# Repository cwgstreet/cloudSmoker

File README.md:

<div align="right">
  
</div>
<br>

---

#  cloudSmoker2

# :construction: **Under Development**

⚠️ **Version 2 Notice:** 
<br>

**This is the active development 
branch for cloudSmoker V2. The original design is now deprecated but remains available on the v1-legacy branch.**

___

# Project Summary

The **cloudSmoker** is a WiFi-enabled barbeque temperature monitor designed to take the guesswork out of low-and-slow cooks. 

Building on the reliable foundation of the original cloudSmoker1 2022 release, Version 2 modernises the platform with a focus on precision, expanded capabilities, and a more comprehensive hardware design.

### What’s New in cloudSmoker2
*   **Expanded Monitoring:** Now supports up to four temperature probes for lager cooks.
*   **Enhanced Precision:** Improved measurement accuracy and response via higher-resolution ADC, optimised bias resistor selection plus improved filtering and ADC management.
*   **Modern Hardware:** Upgraded to a contemporary microcontroller, a refreshed display, and a custom 3D-printed enclosure.
*   **Professional Build:** Transitioning to a custom-manufactured PCB using contemporary SMD (Surface Mount) components for increased reliability and a more compact footprint.
*   **Refined Software:** Features seamless OTA (Over-The-Air) firmware updates, streamlined configuration menus, and robust exception monitoring.

### How it Works
The device tracks critical data points, such as pit and internal meat temperatures, and syncs them to an IoT dashboard. This allows for remote monitoring of real-time graphs and gauges from any browser or smartphone. 

To ensure the cook stays on track, the system sends push notifications if temperatures drift or once the meat reaches its target. The project is designed to be cooker-agnostic, making it a reliable companion for a variety of smokers and BBQ setups.

> ### 🌟 **Update:** cloudSmoker2 development is progressing!
>
1) **Boards now built and firmware port / enhancement is underway.**

<br clear="left"/>
<br>

2) **3D printed enclosure design well advanced**

<br clear="left"/>
<br>

<br>
<br>
<br>
<br>

---

<br>

<br>

# cloudSmoker (v1-legacy) #

## 📜 Legacy Support (Version 1.0)
The original version of this project was based on an **ESP8266** and was built on **Veroboard**. While it is no longer the main focus of development, you can still access all the original files:

*   **[Version 1.0 Release Page](https://github.com/cwgstreet/cloudSmoker/releases/tag/v1.0)**
    *   `Hardware_v1.0.zip`: Includes Fritzing layouts, PDF schematics, and build photos.
    *   `Firmware_v1.0.zip`: The stable code and compiled `.bin` for the original build.

<!-- >**Note:** If you are building this project for the first time, we recommend using the **Version 2** PCB files found in this main branch. -->

**WiFi BBQ Temperature Monitor Project**

[comment]: <> (This project exists as a hands-on opportunity to learn more about electronics, IoT, Arduino / ESP8266 programming, GitHub markdown, etc)

<br>

<p align="center">
  
</p>

### Updates (ver1)
1. **Removed pitTemp probe plug-in checks** - no longer displays LCD error or transmits pitTemp values to ThingSpeak if pit temperature probe is unplugged; necessary to allow pitTemp probe to be unplugged after meat is taken off grill so that resting meat temps can continue to be monitored (common to rest briskett in faux cambo for ~1 hour after removing meat from grill).
<br>
<br>

## Project Summary

The cloudSmoker Barbecue Monitor project is a WiFi-enable temperature monitor.  cloudSmoker is designed to read two temperatures (pit and internal meat temperatures) within my Weber BBQ smoker and upload these to an IOT dashboard, allowing remote cloud monitoring of the cook progress showing temperature vs time graphs, gauges, etc, user-definable cooking notification setpoints and exception push notifications to my smartphone, say if the pit temperatures go outside of acceptable ranges and when the meat is done and ready to be removed.

The overall process flow is conceptualised as follows:

Hardware is based around the NodeMCU (V1.0) ESP8266-12E microcontroller module (for both for WiFi access and microcontroller), two Maverick ET-732/733 thermistor probes, an external ADS1015 "12-bit" ADC, plus a 1602 LCD and rotary encoder for user set-up configuration and display.  Minor thermistor and power filtering was also employed for stability.  

Coding was done using VS Code / PlatformIO IDE platform with data uploaded to ThingSpeak for display and further processing.   Push exception notifications are done through Twitter using Thingspeak's React / ThingTweet functionality.  (:warning: Todo:  export cook logs to Google Sheets).

### Project Overview  ###

An extensive project overview and design process description can be found in the project [Wiki](https://github.com/cwgstreet/cloudSmoker/wiki) covering design goals, hardware, software, etc.  

### Hardware ###

The Hardware folder contains KiCad schematic, PCB board layouts (:warning: TODO) and selected datasheets (including the datasheet for the Semitec 105GT-2 Thermistor, that Maverick customer support kindly provided me.   👏 👍

Note that I have not found this datasheet available anywhere on the web and many other projects incorrectly characterised the Maverick ET-732/733 probes as being based on a 10k ohm thermistor (when it's actually 1M ohm!).  This incorrect assumption frequently led to poor bias resistor selection, resulting in poor measurement accuracy.  As a result, these Maverick thermistors were often not highly regarded.  For example, one project concluded they were [acceptable, but not recommended thermistor choice](https://github.com/CapnBry/HeaterMeter/wiki/HeaterMeter-Probes).   

### cloudSmoker ###

This folder contains the full cloudSmoker software (sketch and libraries); developed under VSCode / Platformio IDE rather than Arduino IDE so folder structure reflect Platformio structure.  Note that the project code base is over 1600 lines total and makes extensive use of user and public libraries.

### Images ###

Self-explanatory

### Project Dashboard ###
A public ThingSpeak [cloudSmoker dashboard](https://thingspeak.com/channels/1679986) is available

### Licence ###

**cloudSmoker (ver1):** MIT Licence.  Note that licence terms have changed for cloudSmoker2 (Ver2)

--- END ---

<br>
<br>

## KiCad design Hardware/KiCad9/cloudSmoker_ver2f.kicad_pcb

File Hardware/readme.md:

# cloudSmoker2 Hardware Reference

This directory serves as the root hardware repository for the **cloudSmoker2** platform. It contains mechanical housing documents, sensor calibration resources, manufacturing documentation, and the complete electronic design suite.

---

## 📂 Repository Structure

```text
├── KiCad9/                          # Core ECAD design environment (KiCad 9.x)
│   ├── cloudSmoker_ver2f.kicad_pro  # Main project configuration
│   ├── cloudSmoker_ver2f.kicad_sch  # 4-Layer Schematic blueprints
│   ├── cloudSmoker_ver2f.kicad_pcb  # Mixed-signal PCB layout 
│   ├── sym-lib-table & fp-lib-table # Local dependency resolution tables
│   ├── JLCImport.pretty/            # Component footprints (.kicad_mod)
│   ├── JLCImport.3dshapes/          # 3D structural clearance models (.step / .wrl)
│   ├── production/                  # Manufacturing artifacts (Gerbers, BOM, CPL)
│   └── svg_files/                   # Dynamic high-resolution hardware dashboard graphics
│
├── Thermistor datasheet/            # High-temperature physical probe reference material
│   ├── ET-732 (Thermistor) datasheet scan.pdf
│   └── Maverick ET-732 - 733 (Semitec 105GT-2 Thermistor) datasheet.pdf
│
├── arduino_housing_01_160717_CAD.PDF.pdf   # Mechanical chassis reference dimensions (cloudSmoker1)
└── licence.md                               # Open-source hardware licensing framework
```

## ⚙️ Key File Subsystems

### 1. Electronic Design Automation (`KiCad9/`)
* **ECAD Engine**: Engineered exclusively inside **KiCad 9**. Backward-compatibility issues can occur if parsed with older software builds.
* **Component Portability**: Component symbols, tracking pads, and 3D packages are completely containerized locally inside the `JLCImport` folders. External global library paths are not required to audit the board.
* **Fabrication Files**: The `KiCad9/production/` subdirectory houses pre-compiled fabrication packages including the zipped Gerber layer arrays, coordinates tables (`positions.csv`), and structural parts listings (`bom.csv`).

### 2. Thermistor Data
* **`Thermistor datasheet/`**: Houses structural lookup sheets for the Semitec 105GT-2 high-temp food probes.

### 3. Physical & Enclosure Overlays
* **`arduino_housing_01_160717_CAD.PDF.pdf`**: Legacy cloudSmoker1 mechanical profile drawing used to verify PCB perimeter cuts, mounting hole positions, and connector face alignments against existing chassis designs.

---

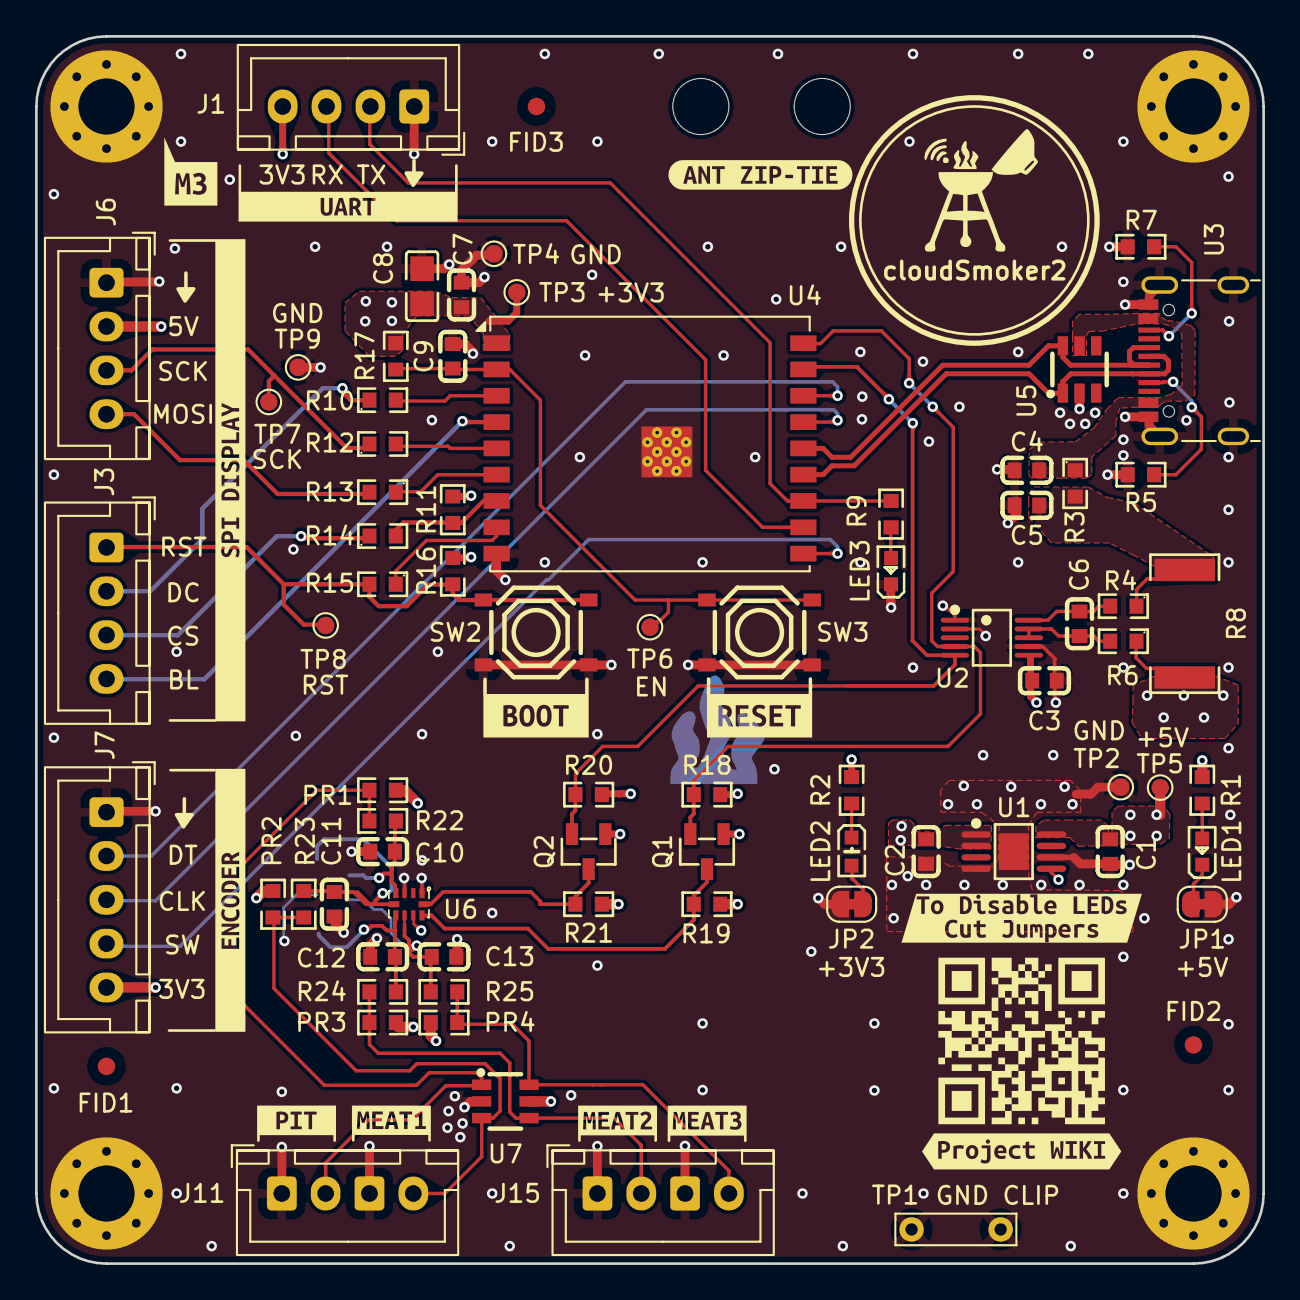
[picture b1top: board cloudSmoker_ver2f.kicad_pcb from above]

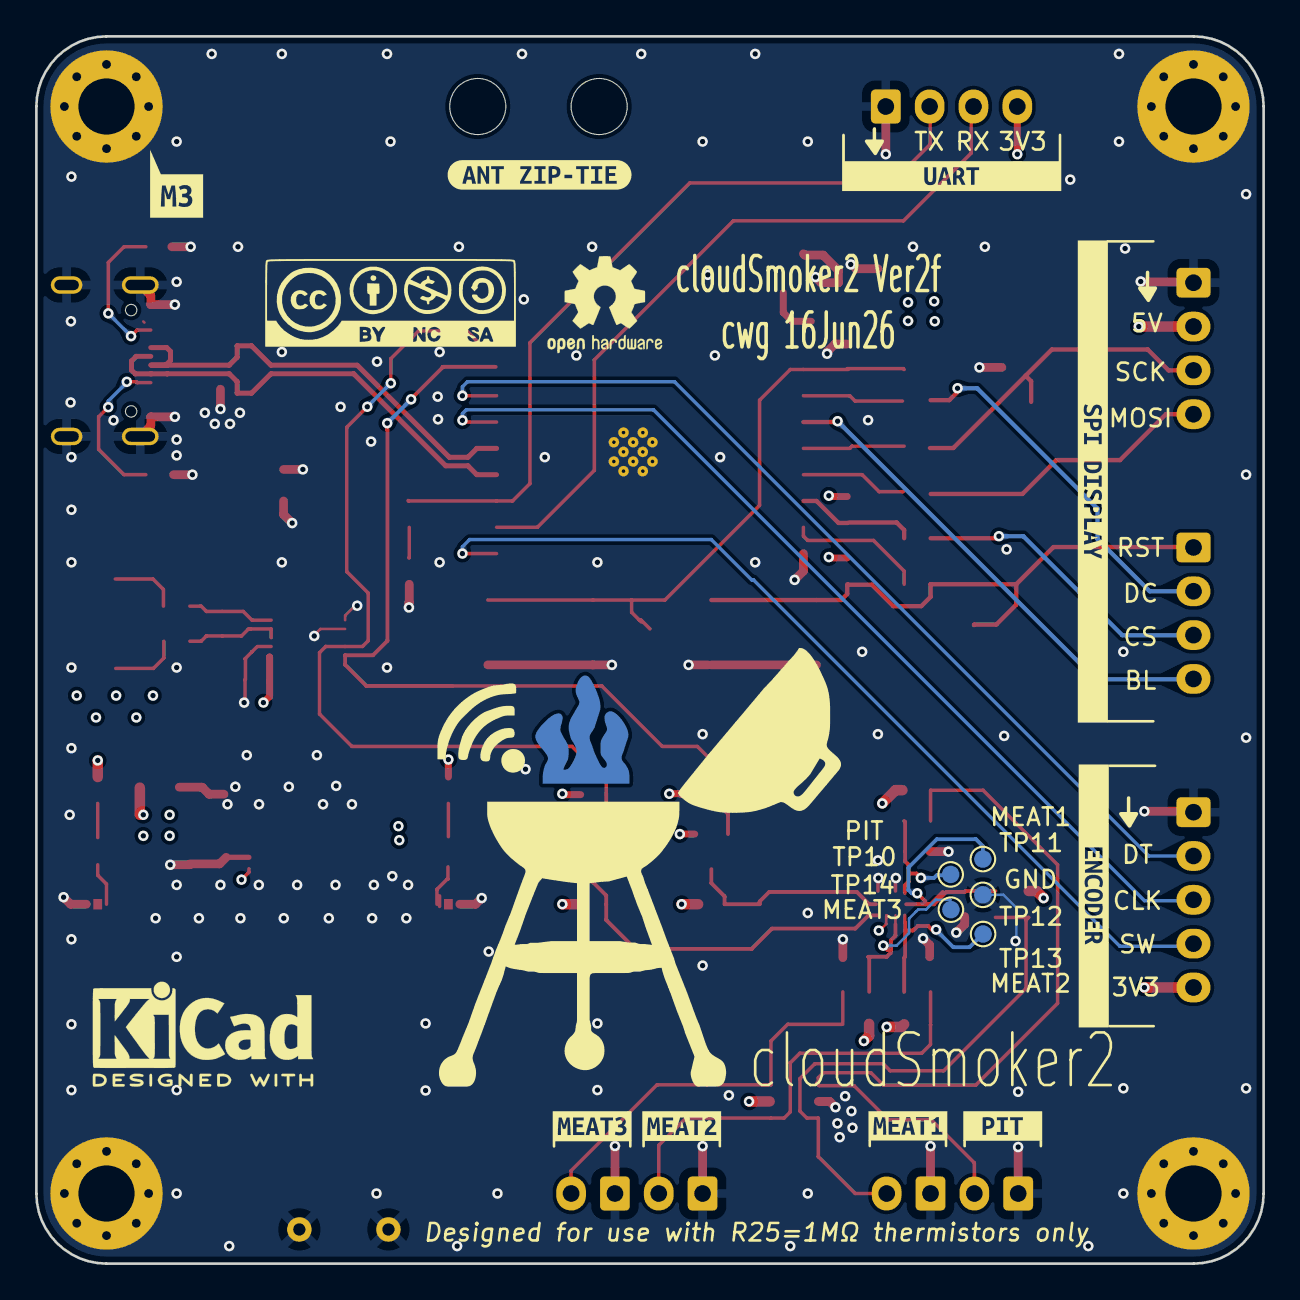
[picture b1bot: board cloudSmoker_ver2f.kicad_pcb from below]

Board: 4 copper layers, 70.0 x 70.0 mm, 110 parts (14 on the bottom side), 45 nets.

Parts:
C1, C9, C10, C11, C12, C13: 1uF; CL10A105KB8NNNC
C2: 2.2uF; CL10A225KO8NNNC
C3, C6, C7: 100nF; CC0603KRX7R9BB104
C4, C5: 470nF; CC0603KRX7R9BB104
C8: 10uF; CL21A106KAYNNNE
FID1, FID2, FID3: Fiducial; Fiducial_1mm_Mask2mm
H1, H2, H3, H4: M3; MountingHole_3.2mm_M3_Pad_Via
H5, H6: M3; MountingHole_3.2mm_M3
J1: Conn_01x02_Pin; JST_XH_B4B-XH-A_1x04_P2.50mm_Vertical
J3, J6: Conn_01x04_Pin; JST_XH_B4B-XH-A_1x04_P2.50mm_Vertical
J7: Conn_01x05; JST_XH_B5B-XH-A_1x05_P2.50mm_Vertical
J11, J15: Conn_01x04_Pin; JST_XH_B4B-XH-A_1x04_P2.50mm_Vertical_two_gnd
JP1, JP2: SolderJumper_2_Bridged; SolderJumper-2_P1.3mm_Bridged_RoundedPad1.0x1.5mm
LED1: Red; KT-0603R
LED2: White; 0603White_light_C2290
LED3: Yellow; FC-1608YXK-585F08
PR1, PR2, PR3, PR4: 120k 0.1%TF; PTFR0603B120KP9
Q1, Q2: BSS138; BSS138_C7420339
QR*****: QR-Code_cloudSmoker_Github_wiki
R1: 2.2k; 0603WAF2201T5E
R2: 1k; 0603WAF1001T5E
R3: 0 ohm; R0603_part-C21189_0-ohm
R4, R6: 10; R0603_part-C22859_10-ohm
R5, R7, R18, R20: 5.1k; 0603WAF5101T5E
R8: 100 mOhm Shunt; RLP25FEER100
R9: 100; 0603WAF1000T5E
R10, R12, R13, R14, R15: 22; R0603_part-C23345
R11, R16, R17, R19, R21, R22, R23, R24, R25: 10k; 0603WAF1002T5E
SW2, SW3: SW_Push_Dual; TS-1187A-B-A-B
TP1: TP_GND_Clip; TestPoint_Bridge_Pitch5.08mm_Drill0.7mm
TP2, TP4, TP9: TP_GND; TestPoint_Pad_D1.0mm
TP3: TP_3V3; TestPoint_Pad_D1.0mm
TP5: TP_5V; TestPoint_Pad_D1.0mm
TP6: TP_EN; TestPoint_Pad_D1.0mm
TP7: TP_SPI_SCK; TestPoint_Pad_D1.0mm
TP8: TP_GIO9; TestPoint_Pad_D1.0mm
TP10: TP_Pit; TestPoint_Pad_D1.0mm
TP11: TP_Meat1; TestPoint_Pad_D1.0mm
TP12: TP_AGND; TestPoint_Pad_D1.0mm
TP13: TP_Meat2; TestPoint_Pad_D1.0mm
TP14: TP_Meat3; TestPoint_Pad_D1.0mm
U1: TLV76733DGNR
U2: INA226AIDGSR
U3: GT-USB-7010ASV; USB_C_Receptacle_G-Switch_GT-USB-7010ASV clipped
U4: ESP32-C3-WROOM-02U-N4; ESP32-C3-WROOM-02U
U5, U7: SRV05-4-P-T7
U6: ADS1115IRUGR
kibuzzard-6A0E9251: G***; kibuzzard-6A0E9251
kibuzzard-6A0E9267: G***; kibuzzard-6A0E9267
kibuzzard-6A1EB0C4, kibuzzard-6A1EB0C4#2: G***; kibuzzard-6A1EB0C4
kibuzzard-6A28B67F, kibuzzard-6A28B67F#2: G***; kibuzzard-6A28B67F
kibuzzard-6A265CBA, kibuzzard-6A265CBA#2: G***; kibuzzard-6A265CBA
kibuzzard-6A265DB6, kibuzzard-6A265DB6#2: G***; kibuzzard-6A265DB6
kibuzzard-6A265E44, kibuzzard-6A265E44#2: G***; kibuzzard-6A265E44
kibuzzard-6A265EBE, kibuzzard-6A265EBE#2: G***; kibuzzard-6A265EBE
kibuzzard-6A266C13: G***; kibuzzard-6A266C13
kibuzzard-6A2660A1, kibuzzard-6A2660A1#2: G***; kibuzzard-6A2660A1
kibuzzard-6A262764, kibuzzard-6A262764#2: G***; kibuzzard-6A262764
kibuzzard-6A266895, kibuzzard-6A266895#2: G***; kibuzzard-6A266895
kibuzzard-6A276479: G***; kibuzzard-6A276479

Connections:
+3.3V: C2.1, C3.1, C7.1, C8.1, J1.4, J7.5, Q1.1 (G), Q2.1 (G), R2.1, R11.1, R16.2, R17.2, R18.2, R20.2, TP3.1, U1.1 (OUT), U1.2 (SNS), U2.6 (VS), U4.1 (3V3)
+5V: C1.1, J6.2, PR1.1, PR2.1, PR3.1, PR4.1, R1.1, R6.1, R8.2, R19.1, R21.1, TP5.1, U1.5 (EN), U1.8 (IN), U6.8 (VDD), U7.5 (VP)
/Load: C6.1, R6.2, U2.8 (Vbus), U2.9 (Vin-)
/MEAT1_IN: J11.4, PR2.2, R23.2, U7.3 (IO2)
/MEAT2_IN: J15.2, PR3.2, R24.2, U7.4 (IO3)
/MEAT3_IN: J15.4, PR4.2, R25.2, U7.6 (IO4)
/PIT_IN: J11.2, PR1.2, R22.2, U7.1 (IO1)
/Supply: C6.2, R4.2, U2.10 (Vin+)
DEBUG_RX: J1.3, U4.11 (IO20/RXD)
DEBUG_TX/LED: J1.2, R9.1, U4.12 (IO21/TXD)
DISP_BL: J3.4, U4.4 (IO5)
DISP_CS: J3.3, R14.1
DISP_DC: J3.2, R10.1
ENC_CLK: J7.3, U4.15 (IO3)
ENC_DT: J7.2, U4.16 (IO2)
ENC_SW: J7.4, U4.10 (IO10)
GND: C1.2, C2.2, C3.2, C4.2, C5.2, C7.2, C8.2, C9.2, C10.1, C11.1, C12.1, C13.1, H1.1, H2.1, H3.1, H4.1, J1.1, J6.1, J7.1, J11.1, J11.3, J15.1, J15.3, JP1.1 (A), JP2.2 (B), LED3.1 (K), R5.2, R7.2, SW2.3, SW2.4, SW3.3, SW3.4, TP1.1, TP2.1, TP4.1, TP9.1, TP12.1, U1.4 (GND), U1.6 (GND), U1.9 (EP), U2.1 (A1), U2.2 (A0), U2.7 (GND), U3.A1 (GND), U3.A12 (GND), U3.B1 (GND), U3.B12 (GND), U3.S1 (SHIELD), U4.9 (GND), U4.19 (GND), U5.2 (VN), U6.1 (ADDR), U6.3 (GND), U7.2 (VN)
I2C_SCL_3V3: Q2.2 (S), R20.1, U2.5 (SCL), U4.17 (IO1)
I2C_SCL_5V: Q2.3 (D), R21.2, U6.10 (SCL)
I2C_SDA_3V3: Q1.2 (S), R18.1, U2.4 (SDA), U4.18 (IO0)
I2C_SDA_5V: Q1.3 (D), R19.2, U6.9 (SDA)
MEAT1: C11.2, R23.1, TP11.1, U6.5 (AIN1)
MEAT2: C12.2, R24.1, TP13.1, U6.6 (AIN2)
MEAT3: C13.2, R25.1, TP14.1, U6.7 (AIN3)
unnamed: JP1.2 (B), LED1.1 (K)
unnamed: JP2.1 (A), LED2.1 (K)
unnamed: LED1.2 (A), R1.2
unnamed: LED2.2 (A), R2.2
unnamed: LED3.2 (A), R9.2
unnamed: R5.1, U3.A5 (CC1)
unnamed: R7.1, U3.B5 (CC2)
unnamed: R10.2, U4.3 (IO4)
unnamed: R12.2, U4.5 (IO6)
unnamed: R13.1, U4.6 (IO7)
unnamed: R11.2, R14.2, U4.7 (IO8)
unnamed: R15.1, U4.8 (IO9)
PIT: C10.2, R22.1, TP10.1, U6.4 (AIN0)
SPI_MOSI: J6.4, R13.2
SPI_SCK: J6.3, R12.1, TP7.1
USB_D+: U3.A6 (D+), U3.B6 (D+), U4.14 (IO19), U5.6 (IO4)
USB_D-: U3.A7 (D-), U3.B7 (D-), U4.13 (IO18), U5.1 (IO1)
VBUS: C4.1, R3.1, U3.A4 (VBUS), U3.A9 (VBUS), U3.B4 (VBUS), U3.B9 (VBUS), U5.5 (VP)
VBUSF: C5.1, R3.2, R4.1, R8.1
~BOOT_DISP_RST: J3.1, R15.2, R16.1, SW2.1, SW2.2, TP8.1
~RESET: C9.1, R17.1, SW3.1, SW3.2, TP6.1, U4.2 (EN)

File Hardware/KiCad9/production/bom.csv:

Designator,Footprint,Quantity,Value,LCSC Part #
"C1, C10, C11, C12, C13, C9",CL10A105KB8NNNC,6,1uF,C15849
C2,CL10A225KO8NNNC,1,2.2uF,C23630
"C3, C6, C7",CC0603KRX7R9BB104,3,100nF,C14663
"C4, C5",CC0603KRX7R9BB104,2,470nF,C1623
C8,CL21A106KAYNNNE,1,10uF,C15850
LED1,KT-0603R,1,Red,C2286
LED2,0603White_light_C2290,1,White,C2290
LED3,FC-1608YXK-585F08,1,Yellow,C89811
"PR1, PR2, PR3, PR4",PTFR0603B120KP9,4,120k 0.1%TF,C351687
"Q1, Q2",BSS138_C7420339,2,BSS138,C7420339
R1,0603WAF2201T5E,1,2.2k,C4190
"R10, R12, R13, R14, R15",R0603_part-C23345,5,22,C23345
"R11, R16, R17, R19, R21, R22, R23, R24, R25",0603WAF1002T5E,9,10k,C25804
"R18, R20, R5, R7",0603WAF5101T5E,4,5.1k,C23186
R2,0603WAF1001T5E,1,1k,C21190
R3,R0603_part-C21189_0-ohm,1,0 ohm,C21189
"R4, R6",R0603_part-C22859_10-ohm,2,10,C22859
R8,RLP25FEER100,1,100 mOhm Shunt,C160587
R9,0603WAF1000T5E,1,100,C22775
"SW2, SW3",TS-1187A-B-A-B,2,SW_Push_Dual,C318884
U1,TLV76733DGNR,1,TLV76733DGNR,C2873382
U2,INA226AIDGSR,1,INA226AIDGSR,C49851
U3,USB_C_Receptacle_G-Switch_GT-USB-7010ASV clipped,1,GT-USB-7010ASV,C2988369
U4,ESP32-C3-WROOM-02U,1,ESP32-C3-WROOM-02U-N4,C2926676
"U5, U7",SRV05-4-P-T7,2,SRV05-4-P-T7,C85364
U6,ADS1115IRUGR,1,ADS1115IRUGR,C2651328

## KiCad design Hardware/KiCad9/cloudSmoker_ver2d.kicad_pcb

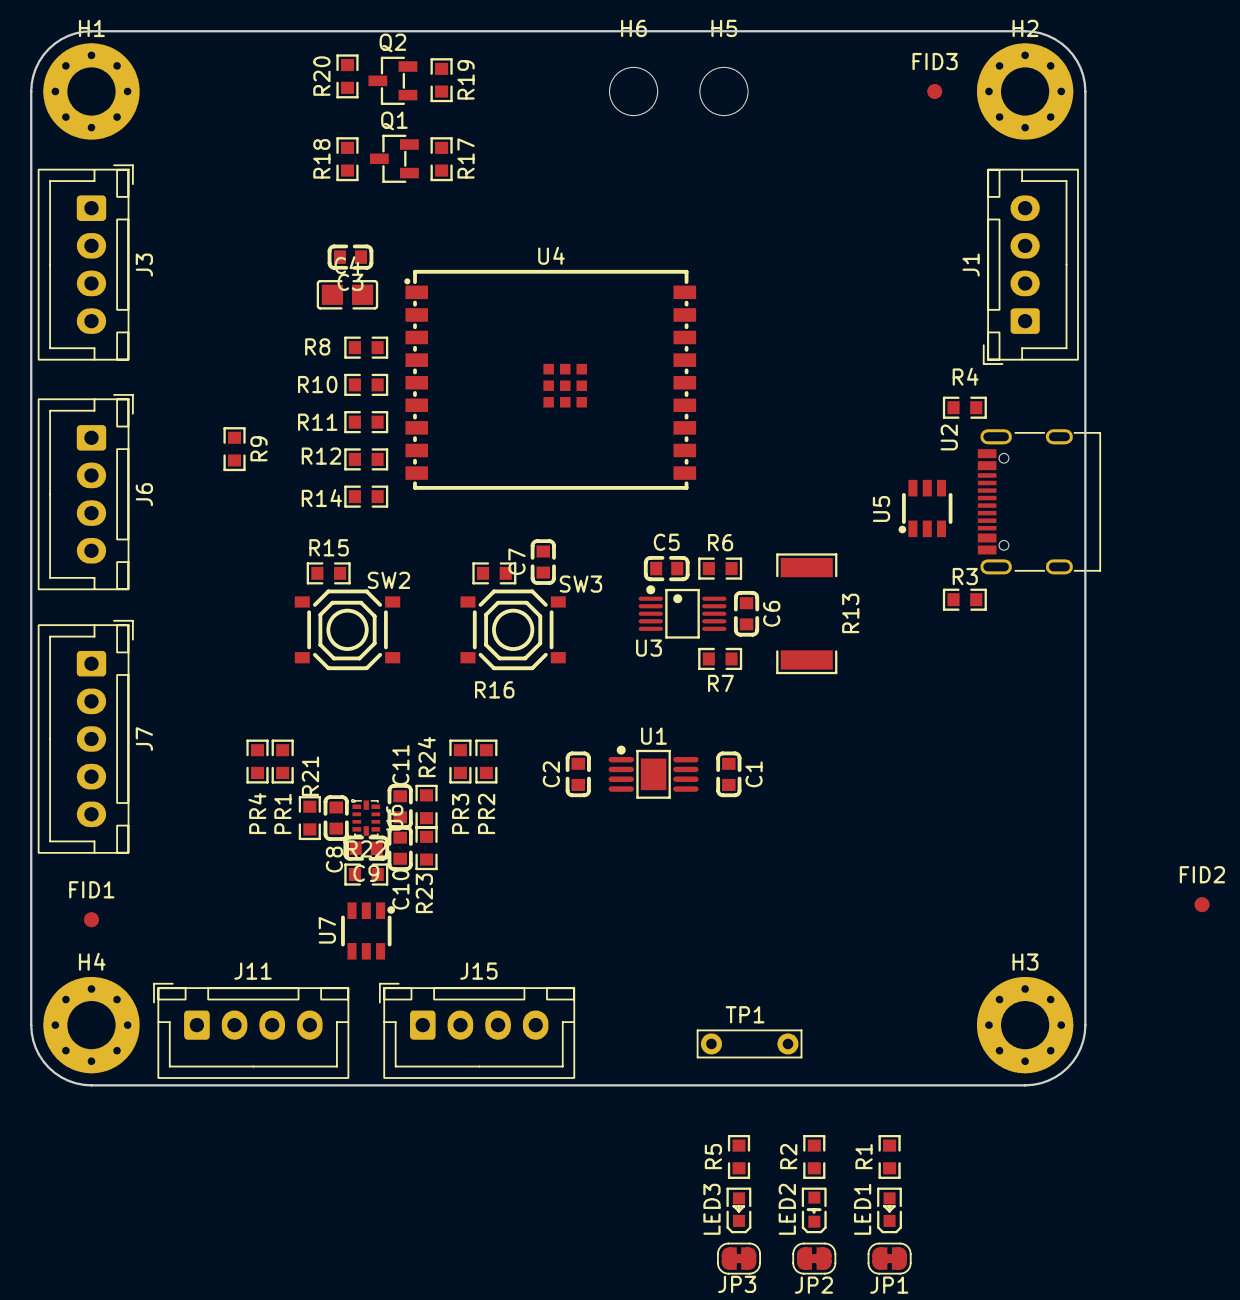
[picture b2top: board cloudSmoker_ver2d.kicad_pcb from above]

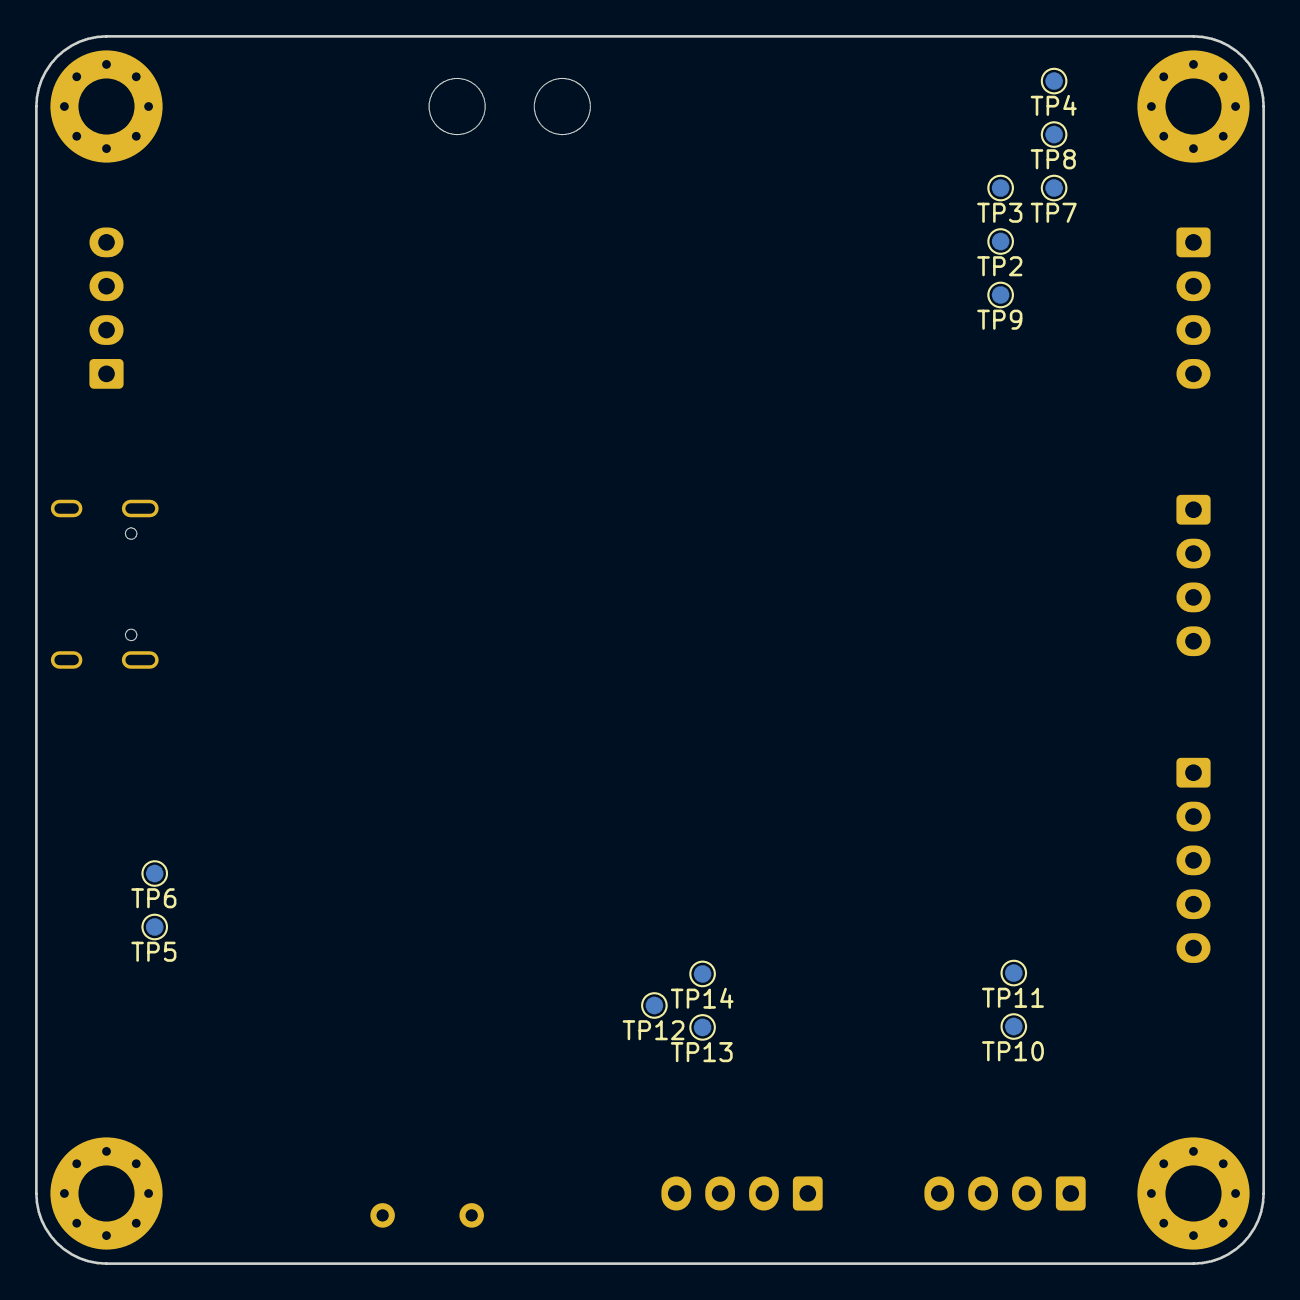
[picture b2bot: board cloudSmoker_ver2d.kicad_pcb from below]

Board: 4 copper layers, 70.0 x 70.0 mm, 85 parts (13 on the bottom side), 45 nets, no tracks yet.

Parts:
C1, C8, C9, C10, C11: 1uF; CL10A105KB8NNNC
C2: 2.2uF; CL10A225KO8NNNC
C3, C5, C6: 100nF; CC0603KRX7R9BB104
C4: 10uF; CL21A106KAYNNNE
C7: 1uF; CC0603KRX7R9BB104
FID1, FID2, FID3: Fiducial; Fiducial_1mm_Mask2mm
H1, H2, H3, H4: M3; MountingHole_3.2mm_M3_Pad_Via
H5, H6: M3; MountingHole_3.2mm_M3
J1: Conn_01x02_Pin; JST_XH_B4B-XH-A_1x04_P2.50mm_Vertical
J3, J6, J11, J15: Conn_01x04_Pin; JST_XH_B4B-XH-A_1x04_P2.50mm_Vertical
J7: Conn_01x05; JST_XH_B5B-XH-A_1x05_P2.50mm_Vertical
JP1, JP2, JP3: SolderJumper_2_Bridged; SolderJumper-2_P1.3mm_Bridged_RoundedPad1.0x1.5mm
LED1: Red; KT-0603R
LED2: White; 0603White_light_C2290
LED3: Yellow; FC-1608YXK-585F08
PR1, PR2, PR3, PR4: 120k 0.1%TF; PTFR0603B120KP9
Q1, Q2: BSS138; BSS138_C7420339
R1: 2.2k; 0603WAF2201T5E
R2: 1k; 0603WAF1001T5E
R3, R4, R17, R19: 5.1k; 0603WAF5101T5E
R5: 100; 0603WAF1000T5E
R6, R7: 10; PTFR0603B120KP9
R8, R10, R11, R12, R14: 22; PTFR0603B120KP9
R9, R15, R16, R18, R20, R21, R22, R23, R24: 10k; 0603WAF1002T5E
R13: 100 mOhm Shunt; RLP25FEER100
SW2, SW3: SW_Push_Dual; TS-1187A-B-A-B
TP1: TP_GND_Clip; TestPoint_Bridge_Pitch5.08mm_Drill0.7mm
TP2: TP_3V3; TestPoint_Pad_D1.0mm
TP3, TP6, TP9: TP_GND; TestPoint_Pad_D1.0mm
TP4: TP_EN; TestPoint_Pad_D1.0mm
TP5: TP_5V; TestPoint_Pad_D1.0mm
TP7: TP_SPI_SCK; TestPoint_Pad_D1.0mm
TP8: TP_GIO9; TestPoint_Pad_D1.0mm
TP10: TP_Pit; TestPoint_Pad_D1.0mm
TP11: TP_Meat1; TestPoint_Pad_D1.0mm
TP12: TP_AGND; TestPoint_Pad_D1.0mm
TP13: TP_Meat2; TestPoint_Pad_D1.0mm
TP14: TP_Meat3; TestPoint_Pad_D1.0mm
U1: TLV76733DGNR
U2: GT-USB-7010ASV; USB_C_Receptacle_G-Switch_GT-USB-7010ASV
U3: INA226AIDGSR
U4: ESP32-C3-WROOM-02U-N4
U5, U7: SRV05-4-P-T7
U6: ADS1115IRUGR

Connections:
+3.3V: C2.1, C3.1, C4.1, C5.1, J1.4, J7.5, Q1.1 (G), Q2.1 (G), R2.1, R9.1, R15.2, R16.2, R17.2, R19.2, TP2.1, U1.1 (OUT), U1.2 (SNS), U3.6 (VS), U4.1 (3V3)
+5V: C1.1, C6.2, J6.2, PR1.1, PR2.1, PR3.1, PR4.1, R1.1, R7.1, R13.2, R18.1, R20.1, TP5.1, U1.5 (EN), U1.8 (IN), U3.8 (Vbus), U5.5 (VP), U6.8 (VDD), U7.5 (VP)
/Load: R7.2, U3.9 (Vin-)
/MEAT1_IN: J11.4, PR2.2, R22.2, U7.3 (IO2)
/MEAT2_IN: J15.2, PR3.2, R23.2, U7.4 (IO3)
/MEAT3_IN: J15.4, PR4.2, R24.2, U7.6 (IO4)
/PIT_IN: J11.2, PR1.2, R21.2, U7.1 (IO1)
/Supply: R6.2, U3.10 (Vin+)
DEBUG_RX: J1.3, U4.11 (IO20/RXD)
DEBUG_TX/LED: J1.2, R5.1, U4.12 (IO21/TXD)
DISP_BL: J3.4, U4.4 (IO5)
DISP_CS: J3.3, R9.2, R12.1
DISP_DC: J3.2, R8.1
ENC_CLK: J7.2, U4.15 (IO3)
ENC_DT: J7.3, U4.16 (IO2)
ENC_SW: J7.4, U4.10 (IO10)
GND: C1.2, C2.2, C3.2, C4.2, C5.2, C7.2, C8.1, C9.1, C10.1, C11.1, H1.1, H2.1, H3.1, H4.1, J1.1, J6.1, J7.1, J11.1, J11.3, J15.1, J15.3, JP1.1 (A), JP2.2 (B), JP3.2 (B), R3.2, R4.2, SW2.3, SW2.4, SW3.3, SW3.4, TP1.1, TP3.1, TP6.1, TP9.1, TP12.1, U1.4 (GND), U1.6 (GND), U1.9 (EP), U2.A1 (GND), U2.A12 (GND), U2.B1 (GND), U2.B12 (GND), U2.S1 (SHIELD), U3.1 (A1), U3.2 (A0), U3.7 (GND), U4.9 (GND), U4.19 (GND), U5.2 (VN), U6.1 (ADDR), U6.3 (GND), U7.2 (VN)
I2C_SCL_3V3: Q2.2 (S), R19.1, U3.5 (SCL), U4.17 (IO1)
I2C_SCL_5V: Q2.3 (D), R20.2, U6.10 (SCL)
I2C_SDA_3V3: Q1.2 (S), R17.1, U3.4 (SDA), U4.18 (IO0)
I2C_SDA_5V: Q1.3 (D), R18.2, U6.9 (SDA)
MEAT1: C9.2, R22.1, TP11.1, U6.5 (AIN1)
MEAT2: C10.2, R23.1, TP13.1, U6.6 (AIN2)
MEAT3: C11.2, R24.1, TP14.1, U6.7 (AIN3)
unnamed: JP1.2 (B), LED1.1 (K)
unnamed: JP2.1 (A), LED2.1 (K)
unnamed: JP3.1 (A), LED3.1 (K)
unnamed: LED1.2 (A), R1.2
unnamed: LED2.2 (A), R2.2
unnamed: LED3.2 (A), R5.2
unnamed: R3.1, U2.A5 (CC1), U5.3 (IO2)
unnamed: R4.1, U2.B5 (CC2), U5.4 (IO3)
unnamed: R8.2, U4.3 (IO4)
unnamed: R10.2, U4.5 (IO6)
unnamed: R11.1, U4.6 (IO7)
unnamed: R12.2, U4.7 (IO8)
unnamed: R14.1, U4.8 (IO9)
PIT: C8.2, R21.1, TP10.1, U6.4 (AIN0)
SPI_MOSI: J6.4, R11.2
SPI_SCK: J6.3, R10.1, TP7.1
USB_D+: U2.A6 (D+), U2.B6 (D+), U4.14 (IO19), U5.6 (IO4)
USB_D-: U2.A7 (D-), U2.B7 (D-), U4.13 (IO18), U5.1 (IO1)
VBUS: C6.1, R6.1, R13.1, U2.A4 (VBUS), U2.A9 (VBUS), U2.B4 (VBUS), U2.B9 (VBUS)
~BOOT_DISP_RST: J3.1, R14.2, R15.1, SW2.1, SW2.2, TP8.1
~RESET: C7.1, R16.1, SW3.1, SW3.2, TP4.1, U4.2 (EN)

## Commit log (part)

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2022-01-02 add static declaration for PROGMEM
2022-01-02 debugging port to esp8266
2022-01-02 debug NodeMCU port
2022-01-02 remove magic numbers for pins in encoder object
2022-01-05 update function
2022-01-05 fix serial bug
2022-01-05 comment out loop problem
2022-01-05 clean up formatting and comments
2022-01-05 clean up
2022-01-05 add debug print statement to moved()
2022-01-06 debug and fixWrapEncoder::moved()
2022-01-06 fixed WrapEncoder::moved() method
2022-01-06 clean up wrapEncoder library
2022-01-06 fix smokerState encoder value bug
2022-01-07 top level of showSettingsMenu() completed
2022-01-07 improve variable names showSplashScreen
2022-01-07 more readable variable names
2022-01-08 code temperature message string routines
2022-01-08 test and update showSettingsMenu
2022-01-10 debugging currentValue and menu button press
2022-01-15 debug smokerState menu display logic WIP
2022-01-16 fix logic of change settings menu
2022-01-16 scaffold final change settings menu
2022-01-16 fixed switch case statements
2022-01-16 work on setTempUnits
2022-01-18 complete setTempUnit routine
2022-01-18 improve menu
2022-01-20 program menu ongoing
2022-01-20 program menu
2022-01-20 fix settings menu temperature unit display bug
2022-01-20 remove old (replaced) refactored code
2022-01-20 work on temp value menu adjustment
2022-01-20 work on settings - change temp targets WIP
2022-01-20 fixed cust char selectArrLeft
2022-01-24 WIP setMeatTemp
2022-01-24 fix cooment
2022-01-24 WIP setMeatDoneTemp
2022-01-24 setMeatTemp working
2022-01-24 setMeatDoneTemp coded
2022-01-24 Complete menu coding and testing
2022-02-04 add breadboard images
2022-02-17 add and test ads1015 i2c ADC
2022-02-19 code cwg_ads1x15 lib
2022-02-23 minor updates
2022-02-24 coding steinhartHart library (WIP)
2022-02-24 work on steinhart hart
2022-02-24 sh library changes
2022-02-26 minor comment change
2022-02-28 code shh library
2022-02-28 fix header guards
2022-02-28 code steinhart hart lib
2022-03-02 update library includes
2022-03-04 fix [-Wreorder] warnings
2022-03-05 SHH updates for temp probe testing
2022-03-06 pio code inspect changes
2022-03-09 debug and fix memory leak in medianFilterLib2
2022-03-10 restructure folders (dump old files)
2022-03-10 remove
2022-03-10 remove files now on .gitignore
2022-03-10 update flow diagram v2
2022-03-10 clean up library includes
2022-03-12 debugging cwg_shh library
2022-03-12 degugging shh lib - not fixed
2022-03-13 refactor SHH lib to accept measured voltage
2022-03-13 refactor shh lib to accept measured supply voltage
2022-03-17 minor library refactoring
2022-03-17 library refactoring
2022-03-19 Update SHH constants
2022-03-19 Minor code and comment cleanup
2022-03-19 Update .gitnore for secrets.h lib
2022-03-19 add new temp error images
2022-03-19 add include secrets.h to myConstants lib
2022-03-20 clean up surplus images
2022-03-20 add secrets.h lib for confidential info
2022-03-20 sort out mySecrets.lib
2022-03-29 add temp offsets
2022-03-29 remove uneccesary images
2022-03-29 add images
2022-03-29 change build type to prod
2022-03-30 fix SHH calculation bug re constants
2022-03-31 add temp offset correction constants
2022-04-02 update libraries
2022-04-02 add ESPAsync_WiFiManager lib depens
2022-04-07 set up WifiManager and cwg_wifi libs
2022-04-07 cleaned up as moved to wifi manager approach
2022-04-07 minor clean-up
2022-04-08 minor code refactor
2022-04-08 update helper functions with getElapsedCookTime_ms
2022-04-10 refactor sprintf to snprintf - no buffer overflow
2022-04-10 refactor sprintf to snprintf
2022-04-10 change starting current pitTemp
2022-04-10 minor config change
2022-04-10 code LCD::showBBQStatusScreen()
2022-04-10 code bbqStatus and modemSleep states
2022-04-10 code sleep behaviour
2022-04-10 fix debugging comment
2022-04-10 code getTemp state
2022-04-10 rename modemSleep to Sleep case
2022-04-10 code txTemps and update sleep states
2022-04-12 reinstate debug mode code
2022-04-12 set up ThingSpeak
2022-04-14 working on post-settings stae machine
2022-04-15 fixed flash problem
2022-04-15 debugging post-setup State problems
2022-04-15 code post-setup state machine
2022-04-15 finish psot-setting SM coding
2022-04-15 code BBQStatus state
2022-04-15 fix txTemps state to thingSpeak
2022-04-16 minor code cleanup
2022-04-16 update webpage
2022-04-16 branch update
2022-04-16 change webpage to docs folder
2022-04-18 added dashboard image
2022-04-18 add images for readme
2022-04-18 rename img to get rid of spaces
2022-04-18 img update
2022-04-18 update img
2022-04-18 new image
2022-04-18 update thingspeak badge
    logo and link
2022-04-18 update badge
2022-04-18 bring readme up to date
2022-04-18 fix badge link
2022-04-18 remove img
2022-04-18 rel path from permalink
2022-04-18 wording improvements
2022-04-19 update icon
2022-04-19 sync images
2022-04-19 upate readme
2022-04-19 update readme with imgs
2022-04-19 adjust image
2022-04-19 update images
2022-04-19 dark / light theme image
2022-04-19 update light image
2022-04-20 add image
2022-04-20 update image
2022-04-26 update prototype schematic
2022-04-26 update schematic pdf
2022-04-26 update schematic
2022-04-26 add construction images
2022-04-27 add fritzing image
2022-04-28 file changes
2022-08-06 minor edits
2022-08-06 fix typos
2022-08-09 Update README.md
    Fix typo
2022-09-25 Remove probe plug-in check
2022-09-25 add new revision section at top
2022-11-09 mistake
2023-11-01 update to ignore OpenLibre files
2023-12-11 fix misspelled peripherals
2023-12-11 spell check and fix comment typos
2023-12-13 fix spelling typos
2026-04-05 create Ver1 tag
2026-04-12 Update README with version 2 notice
    Added version notice for cloudSmoker V2 and deprecated original design.
2026-04-12 create ver1 release
2026-04-12 update version
2026-04-12 Document legacy support for Version 1.0
    Added legacy support section for Version 1.0 with links to release pages.
2026-04-16 Add Ver1 Hackaday featured badge to README
    Added a badge for being featured on Hackaday.
2026-04-16 Revise README for clarity and updates
    Updated README to remove redundant Hackaday badge and added a new update regarding pitTemp probe functionality.
2026-04-16 Update legacy support description in README
2026-04-16 Fix formatting and emoji in Hardware section of README
    Updated text formatting and corrected emoji usage in the Hardware section.
2026-04-17 Update image files for Ver2
2026-04-17 rename image file
2026-04-17 update images files
2026-04-18 add Steinhart-hart
2026-04-27 update kicad cloudSmoker_ver2 files
2026-04-27 kicad updates
2026-04-28 kicad schematic updates
2026-05-01 cloudSmoker schematic ver2b changes
2026-05-06 update .gitignore to ignore "depreciated" files (usually old working versions)
2026-05-06 remove "depreciated" files (usually old working versions)
2026-05-06 remove depreciated files from git tracking
2026-05-06 remove depreciated files
2026-05-06 change the .gitignore f
2026-05-06 streamline .gitignore
2026-05-06 Refresh gitignore
2026-05-06 create version 2c
2026-05-06 create ver2C and archive ver2B as deprecated
2026-05-19 update board files for v2d
2026-05-22 update hardware files for version 2e
2026-05-24 update hardware version number to 2f
2026-06-01 Update cloudSmoker_ver2f
2026-06-07 Revise licensing terms for cloudSmoker2 project
    Updated licensing terms to reflect mixed copyleft and non-commercial open-source model for the cloudSmoker project, detailing specific licenses for firmware, hardware, and enclosure files.
2026-06-07 Add license information for hardware files
2026-06-07 update hardware files for v2f
2026-06-07 add Enclosure/licence.md
2026-06-07 enclosure licence terms added
2026-06-07 update file structure
2026-06-07 Revise license details for cloudSmoker
    Updated license information for cloudSmoker.
2026-06-07 Update README with project details and images
    Added project description and images to README.
2026-06-07 add licence hields for cloudSmoker2
2026-06-07 Revise README for Version 2 and legacy support
    Updated README to reflect the active development of Version 2 and deprecated status of Version 1.
2026-06-07 removed new icon for Ver1 update
    Updated the README to remove unnecessary HTML entities and clarified the updates section.
2026-06-12 hardware updates
2026-06-12 update cloudsmoker2 graphic to orange flame
2026-06-12 change name of image file
2026-06-12 Revise image links and update section title to 'Updates (ver1)'
    Updated README to modify image references and section titles.
2026-06-14 update hardware files for cloudSmoker_ver2f
2026-06-18 updated: Hardware/KiCad9/cloudSmoker_ver2f.kicad_pcb
2026-06-18 hardware: update cloudSmoker_ver2f
2026-06-18 move schematic images
2026-06-18 rename: cloudSmoker_ver2f.kicad_pcb -> ~cloudSmoker_ver2f.kicad_pcb
2026-06-19 clean up files
2026-06-19 update .gitignore for kicad9 files
2026-06-19 file cleanup
2026-06-19 restore mistakenly deleted files
2026-06-19 Create readme.md for Kicad9 production directory
    Added a readme file explaining the purpose and contents of the directory.
2026-06-19 Add hardware reference documentation for cloudSmoker2
    This file serves as a comprehensive hardware reference for the cloudSmoker2 platform, detailing the repository structure, key subsystems, and artifacts related to electronic design, physical enclosur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
2026-06-19 Update readme.md for subsystem and artifact sections
2026-06-19 Fix typo in Thermistor section heading
2026-06-21 Update README with cloudSmoker V2 project summary
    Added project summary and details about cloudSmoker V2 features.
2026-06-21 new file: Images/CloudSmoker2 graphic.png
2026-06-21 Add development status indication to README
2026-06-21 Update README with version notice and badges
    Added version notice and restored license badges.
2026-06-27 configure platformio.ini for breadboad and pcb environments (Gemini AI assist)
2026-06-27 add repomix and xml to .gitignore
2026-06-27 update repomix ignore
2026-06-28 fix periphials spelling error
2026-06-28 update test code for wrapEncoder library
2026-06-28 add USB and monitor port setting to breadboard environment in platformio
2026-06-30 restore main_breadboard-test.cpp (remove comments)
2026-06-30 update schematic audio jack symbol
2026-06-30 add breadboard images for cloudSmoker2
2026-06-30 add annotated breadboard image
2026-06-30 fix platformio.ini pin assignments for encoder and display
2026-06-30 replace platforio.ini to get rid of typos

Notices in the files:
README.md:
GPLv3
CC BY-NC-SA 4.0
